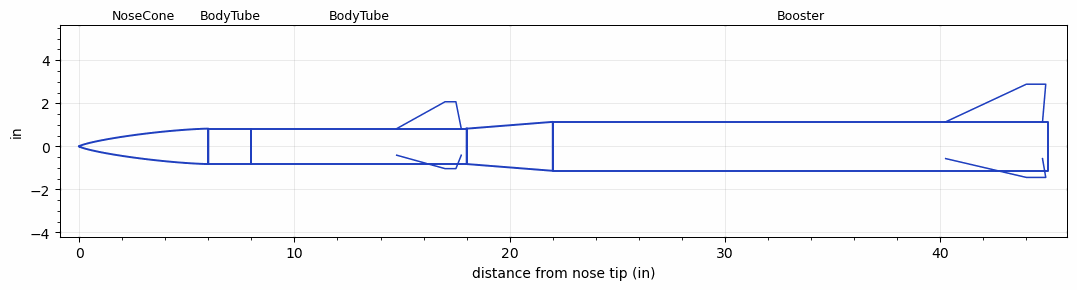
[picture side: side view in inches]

<RASAeroDocument>
 <FileVersion>2</FileVersion>
 <RocketDesign>
  <NoseCone>
   <Length>6</Length>
   <Diameter>1.644</Diameter>
   <Shape>Von Karman Ogive</Shape>
   <Location>0</Location>
  </NoseCone>
  <BodyTube>
   <Length>2</Length>
   <Diameter>1.644</Diameter>
   <Location>6</Location>
  </BodyTube>
  <BodyTube>
   <Length>10</Length>
   <Diameter>1.644</Diameter>
   <Location>8</Location>
   <Fin>
    <Count>3</Count>
    <Chord>3</Chord>
    <Span>1.25</Span>
    <SweepDistance>2.25</SweepDistance>
    <TipChord>0.5</TipChord>
    <Thickness>0.125</Thickness>
    <LERadius>0.05</LERadius>
    <Location>3.25</Location>
    <AirfoilSection>Hexagonal</AirfoilSection>
    <FX1>0.25</FX1>
    <FX3>0.3</FX3>
   </Fin>
  </BodyTube>
  <Booster>
   <Length>23</Length>
   <Diameter>2.274</Diameter>
   <InsideDiameter>1.644</InsideDiameter>
   <Location>18</Location>
   <ShoulderLength>4</ShoulderLength>
   <Fin>
    <Count>3</Count>
    <Chord>4.5</Chord>
    <Span>1.75</Span>
    <SweepDistance>3.75</SweepDistance>
    <TipChord>0.9</TipChord>
    <Thickness>0.125</Thickness>
    <LERadius>0.05</LERadius>
    <Location>4.75</Location>
    <AirfoilSection>Hexagonal</AirfoilSection>
    <FX1>0.25</FX1>
    <FX3>0.3</FX3>
   </Fin>
  </Booster>
  <Surface>Camouflage Paint</Surface>
  <ModifiedBarrowman>True</ModifiedBarrowman>
  <Turbulence>True</Turbulence>
  <UseBooster1>True</UseBooster1>
  <UseBooster2>False</UseBooster2>
 </RocketDesign>
 <LaunchSite>
  <Altitude>850</Altitude>
  <Pressure>29.08</Pressure>
  <RodAngle>0</RodAngle>
  <RodLength>72</RodLength>
  <Temperature>70</Temperature>
  <WindSpeed>6</WindSpeed>
 </LaunchSite>
 <Recovery>
  <Altitude1>700</Altitude1>
  <Altitude2>656.168</Altitude2>
  <DeviceType1>Parachute</DeviceType1>
  <DeviceType2>Parachute</DeviceType2>
  <Event1>True</Event1>
  <Event2>True</Event2>
  <Size1>18</Size1>
  <Size2>35.9999</Size2>
  <EventType1>Altitude</EventType1>
  <EventType2>Apogee</EventType2>
  <CD1>0.5</CD1>
  <CD2>0</CD2>
 </Recovery>
 <SimulationList>
  <Simulation>
   <SustainerEngine>Dart  (NoThrust)</SustainerEngine>
   <SustainerLaunchWt>1.68</SustainerLaunchWt>
   <SustainerCG>10.29</SustainerCG>
   <SustainerIgnitionDelay>0</SustainerIgnitionDelay>
   <Booster1Engine>J500G  (AT)</Booster1Engine>
   <Booster1LaunchWt>4.86</Booster1LaunchWt>
   <Booster1SeparationDelay>0</Booster1SeparationDelay>
   <Booster1IgnitionDelay>0</Booster1IgnitionDelay>
   <Booster1CG>24.83</Booster1CG>
   <IncludeBooster1>True</IncludeBooster1>
   <Booster2Delay>0</Booster2Delay>
   <IncludeBooster2>False</IncludeBooster2>
   <TimetoApogee>21.02035</TimetoApogee>
   <MaxAltitude>8661.782</MaxAltitude>
   <MaxVelocity>1048.699</MaxVelocity>
  </Simulation>
  <Simulation>
   <SustainerLaunchWt>1.6788</SustainerLaunchWt>
   <SustainerCG>10.2911</SustainerCG>
   <SustainerIgnitionDelay>0</SustainerIgnitionDelay>
   <Booster1LaunchWt>5.1265</Booster1LaunchWt>
   <Booster1SeparationDelay>0</Booster1SeparationDelay>
   <Booster1IgnitionDelay>0</Booster1IgnitionDelay>
   <Booster1CG>25.1193</Booster1CG>
   <IncludeBooster1>True</IncludeBooster1>
   <Booster2Delay>0</Booster2Delay>
   <IncludeBooster2>False</IncludeBooster2>
  </Simulation>
  <Simulation>
   <SustainerLaunchWt>1.6788</SustainerLaunchWt>
   <SustainerCG>10.2911</SustainerCG>
   <SustainerIgnitionDelay>0</SustainerIgnitionDelay>
   <Booster1LaunchWt>3.4109</Booster1LaunchWt>
   <Booster1SeparationDelay>0</Booster1SeparationDelay>
   <Booster1IgnitionDelay>0</Booster1IgnitionDelay>
   <Booster1CG>19.0366</Booster1CG>
   <IncludeBooster1>True</IncludeBooster1>
   <Booster2Delay>0</Booster2Delay>
   <IncludeBooster2>False</IncludeBooster2>
  </Simulation>
 </SimulationList>
</RASAeroDocument>
